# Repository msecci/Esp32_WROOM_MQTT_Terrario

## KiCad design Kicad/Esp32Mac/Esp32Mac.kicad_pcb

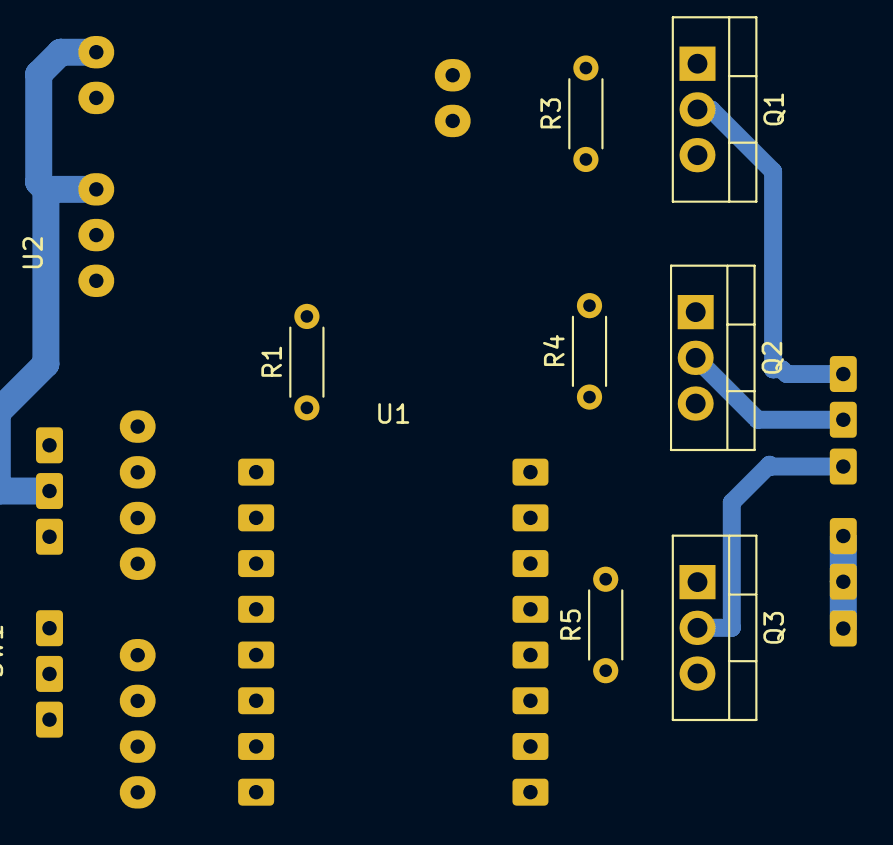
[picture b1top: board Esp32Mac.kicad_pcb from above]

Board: 2 copper layers, 10 parts (0 on the bottom side), 10 nets.

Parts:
Q1, Q2, Q3: TIP120; TO-220-3_Vertical
R1: 10k; R_Axial_DIN0204_L3.6mm_D1.6mm_P5.08mm_Horizontal
R3, R4, R5: 220; R_Axial_DIN0204_L3.6mm_D1.6mm_P5.08mm_Horizontal
SW1: SW_DIP_SPSTx02_Piano_10.8x6.64mm_W7.62mm_P2.54mm
U1: ESP32-C3; ESP32-C3-WROOM-02U
U2: DHT11; Aosong_DHT11_5.5x12.0_P2.54mm

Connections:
GNDREF: Q1.3 (E), Q2.3 (E), Q3.3 (E), SW1.GNDREF, U1.GND, U2.GDNREF, U2.GNDREF
LED1: R3.1, U1.GPI01
LED2: R4.1, U1.GPI04
LED3: R5.1, U1.GPI03
NEXTKEY: SW1.SW3, U1.GPI08
unnamed: Q1.1 (B), R3.2
unnamed: Q2.1 (B), R4.2
unnamed: Q3.1 (B), R5.2
PREVKEY: SW1.SW2, U1.GPI09
SELECTKEY: SW1.SW1, U1.GPI06

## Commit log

2025-10-18 Inizializzazione repository
2025-10-19 Aggiornati pin
2025-10-19 aggiornato kicad
2025-10-20 uff01
2025-10-20 uff02
2025-10-21 libreria TFT_eSPI
2025-10-21 Refactor display handling for TFT_eSPI
2025-10-21 user-setup.h
2025-10-21 Replace Adafruit text bounds calls with TFT_eSPI equivalents
2025-10-21 modificati i riferimenti ai colori
2025-10-21 casa01
2025-10-22 doc01
2025-10-22 Fix MQTT payload copying to avoid out-of-bounds
2025-10-22 casa02
2025-10-22 casa03
2025-10-23 kicad
2025-10-23 uff04
